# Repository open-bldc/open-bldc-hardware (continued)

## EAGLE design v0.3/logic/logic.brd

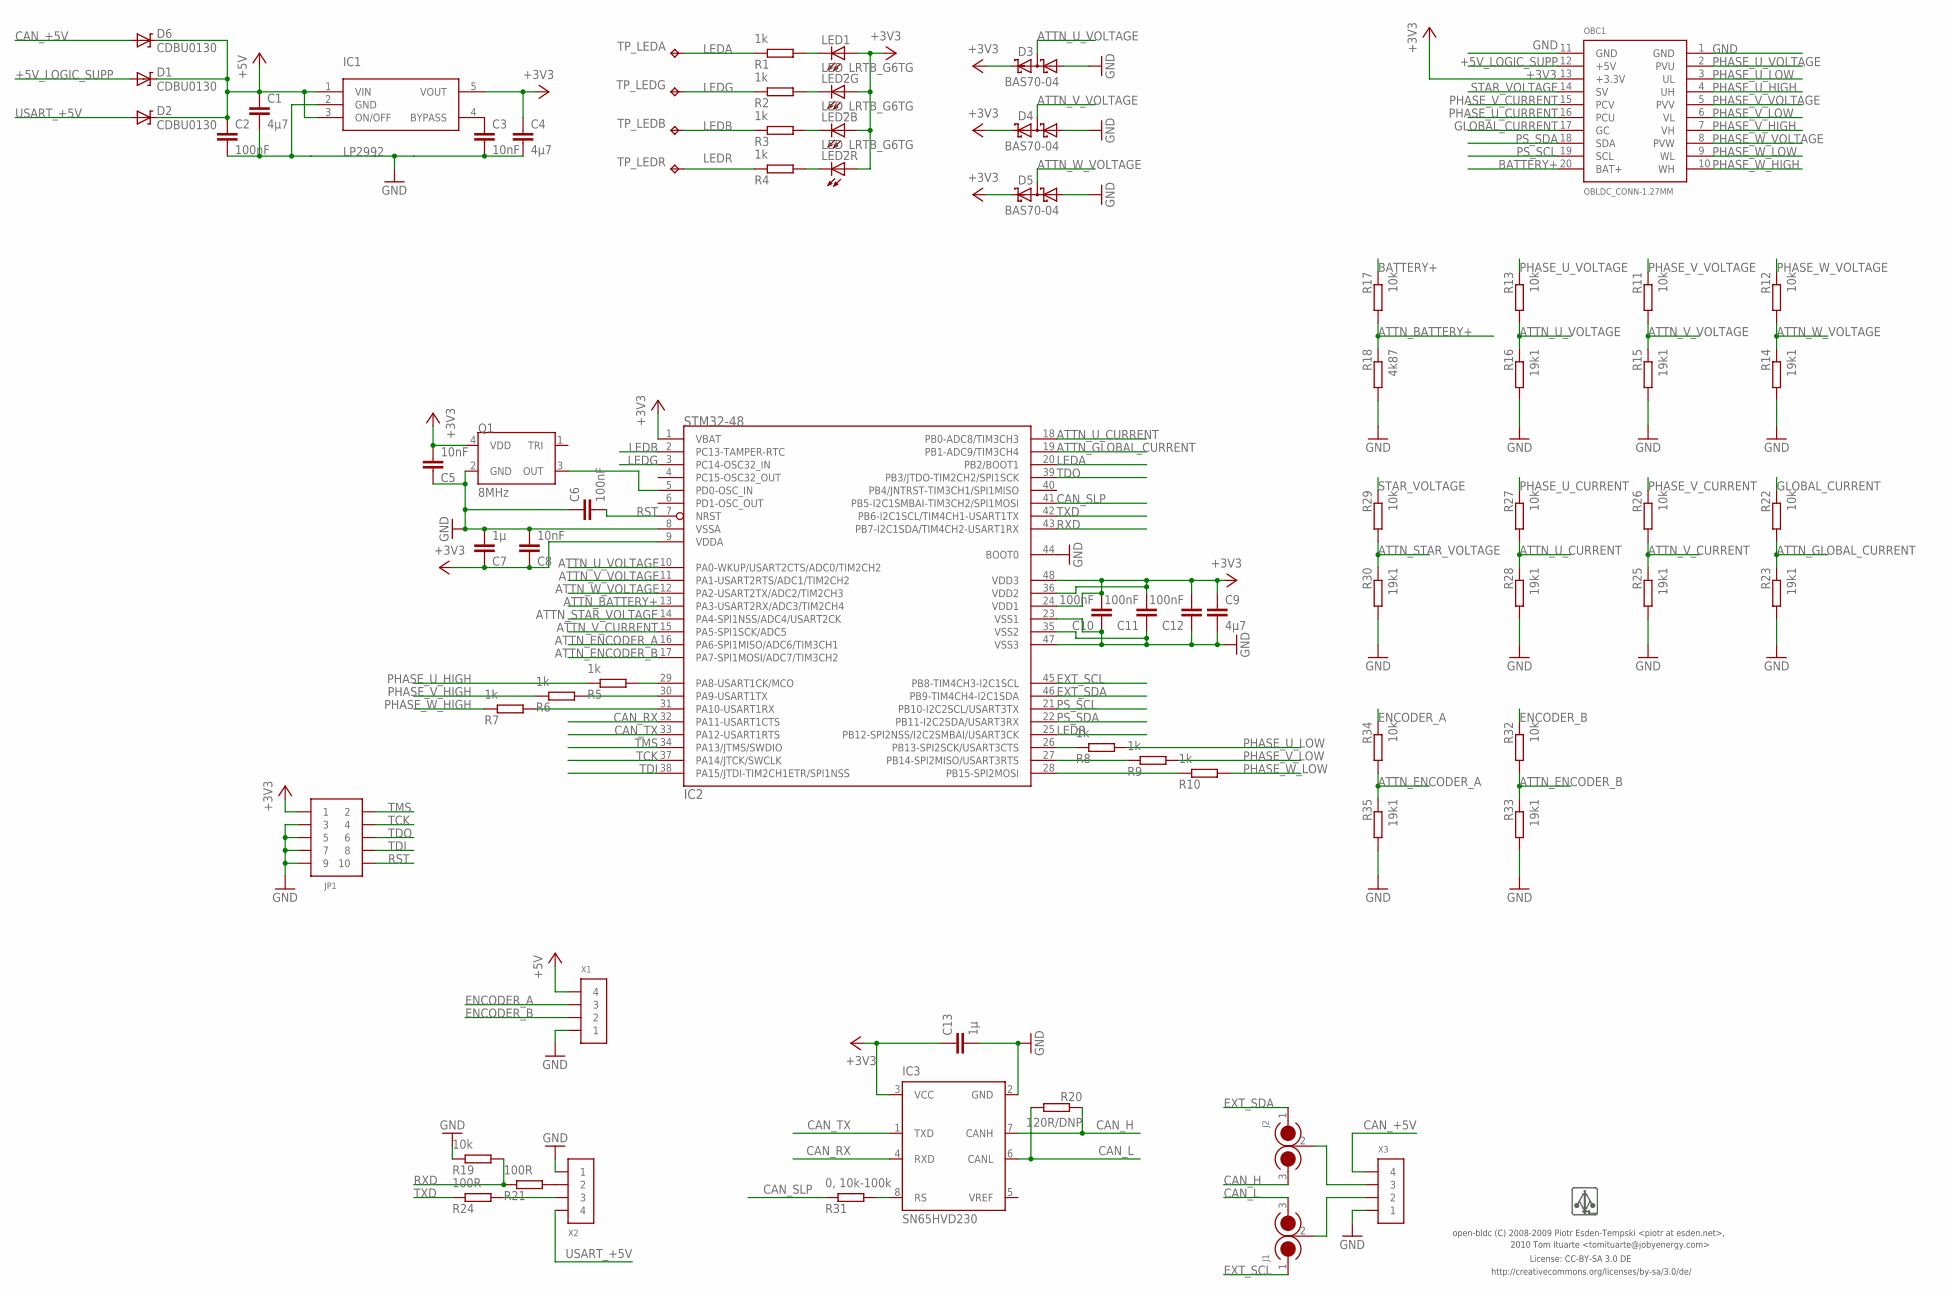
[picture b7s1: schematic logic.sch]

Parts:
C1, C4, C9: 4µ7; 0603-CAP
C2, C6, C10, C11, C12: 100nF; 0603-CAP
C3, C5, C8: 10nF; 0603-CAP
C7, C13: 1µ; 0603-CAP
D1, D2, D6: CDBU0130; 0603-LED
D3, D4, D5: BAS70-04; SOT23
IC1: LP2992; SOT23-5
IC2: STM32-48; LQFP48
IC3: SN65HVD230; SO8
J1, J2: CIRC_JMP_2
JP1: PIN_HDR_EDG_1.27MM_5-2-DH; PIN_HDR_1.27MM_SMD_DH_10
LED1: AMBER; 0603-LED
LED2: LED_LRTB_G6TG; PLCC6
OBC1: OBLDC_CONN-1.27MM; OBLDC_CONN
Q1: 8MHz; ASE_OSCILLATOR
R1, R2, R3, R4, R5, R6, R7, R8, R9, R10: 1k; 0603-RES
R11, R12, R13, R17, R19, R22, R26, R27, R29, R32, R34: 10k; 0603-RES
R14, R15, R16, R23, R25, R28, R30, R33, R35: 19k1; 0603-RES
R18: 4k87; 0603-RES
R20: 120R/DNP; 0603-RES
R21, R24: 100R; 0603-RES
R31: 0, 10k-100k; 0603-RES
TP_LEDA: TP-SMD; MINI_TESTPAD
TP_LEDB: TP-SMD; MINI_TESTPAD
TP_LEDG: TP-SMD; MINI_TESTPAD
TP_LEDR: TP-SMD; MINI_TESTPAD
U$1: LOGO
X1, X2, X3: CONN_4-1-53261; PB-53261-04

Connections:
+3V3: C4.P$1 (1), C5.P$2 (2), C7.P$1 (1), C8.P$1 (1), C9.P$1 (1), C10.P$2 (2), C11.P$2 (2), C12.P$2 (2), C13.P$1 (1), D3.2 (C2), D4.2 (C2), D5.2 (C2), IC1.5 (VOUT), IC2.1 (VBAT), IC2.9 (VDDA), IC2.24 (VDD1), IC2.36 (VDD2), IC2.48 (VDD3), IC3.3 (VCC), JP1.1, LED1.A, LED2.A1 (A), LED2.A2 (A), LED2.A3 (A), OBC1.13 (+3.3V), Q1.4 (VDD)
+5V: C1.P$1 (1), C2.P$1 (1), D1.C, D2.C, D6.C, IC1.1 (VIN), IC1.3 (ON/OFF), X1.4
+5V_LOGIC_SUPP: D1.A, OBC1.12 (+5V)
ATTN_BATTERY+: IC2.13 (PA3-USART2RX/ADC3/TIM2CH4), R17.P$2 (2), R18.P$1 (1)
ATTN_ENCODER_A: IC2.16 (PA6-SPI1MISO/ADC6/TIM3CH1), R34.P$2 (2), R35.P$1 (1)
ATTN_ENCODER_B: IC2.17 (PA7-SPI1MOSI/ADC7/TIM3CH2), R32.P$2 (2), R33.P$1 (1)
ATTN_GLOBAL_CURRENT: IC2.19 (PB1-ADC9/TIM3CH4), R22.P$2 (2), R23.P$1 (1)
ATTN_STAR_VOLTAGE: IC2.14 (PA4-SPI1NSS/ADC4/USART2CK), R29.P$2 (2), R30.P$1 (1)
ATTN_U_CURRENT: IC2.18 (PB0-ADC8/TIM3CH3), R27.P$2 (2), R28.P$1 (1)
ATTN_U_VOLTAGE: D3.3 (C1A2), IC2.10 (PA0-WKUP/USART2CTS/ADC0/TIM2CH2), R13.P$2 (2), R16.P$1 (1)
ATTN_V_CURRENT: IC2.15 (PA5-SPI1SCK/ADC5), R25.P$1 (1), R26.P$2 (2)
ATTN_V_VOLTAGE: D4.3 (C1A2), IC2.11 (PA1-USART2RTS/ADC1/TIM2CH2), R11.P$2 (2), R15.P$1 (1)
ATTN_W_VOLTAGE: D5.3 (C1A2), IC2.12 (PA2-USART2TX/ADC2/TIM2CH3), R12.P$2 (2), R14.P$1 (1)
BATTERY+: OBC1.20 (BAT+), R17.P$1 (1)
CAN_+5V: D6.A, X3.4
CAN_H: IC3.7 (CANH), J2.3, R20.P$1 (1)
CAN_L: IC3.6 (CANL), J1.3, R20.P$2 (2)
CAN_RX: IC2.32 (PA11-USART1CTS), IC3.4 (RXD)
CAN_SLP: IC2.41 (PB5-I2C1SMBAI-TIM3CH2/SPI1MOSI), R31.P$1 (1)
CAN_TX: IC2.33 (PA12-USART1RTS), IC3.1 (TXD)
ENCODER_A: R34.P$1 (1), X1.3
ENCODER_B: R32.P$1 (1), X1.2
EXT_SCL: IC2.45 (PB8-TIM4CH3-I2C1SCL), J1.1
EXT_SDA: IC2.46 (PB9-TIM4CH4-I2C1SDA), J2.1
GLOBAL_CURRENT: OBC1.17 (GC), R22.P$1 (1)
GND: C1.P$2 (2), C2.P$2 (2), C3.P$2 (2), C4.P$2 (2), C5.P$1 (1), C6.P$1 (1), C7.P$2 (2), C8.P$2 (2), C9.P$2 (2), C10.P$1 (1), C11.P$1 (1), C12.P$1 (1), C13.P$2 (2), D3.1 (A1), D4.1 (A1), D5.1 (A1), IC1.2 (GND), IC2.8 (VSSA), IC2.23 (VSS1), IC2.35 (VSS2), IC2.44 (BOOT0), IC2.47 (VSS3), IC3.2 (GND), JP1.3, JP1.5, JP1.7, JP1.9, OBC1.1 (GND), OBC1.11 (GND), Q1.2 (GND), R14.P$2 (2), R15.P$2 (2), R16.P$2 (2), R18.P$2 (2), R19.P$1 (1), R23.P$2 (2), R25.P$2 (2), R28.P$2 (2), R30.P$2 (2), R33.P$2 (2), R35.P$2 (2), X1.1, X2.1, X3.1
LEDA: IC2.20 (PB2/BOOT1), R1.P$1 (1), TP_LEDA.1
LEDB: IC2.2 (PC13-TAMPER-RTC), R3.P$1 (1), TP_LEDB.1
LEDG: IC2.3 (PC14-OSC32_IN), R2.P$1 (1), TP_LEDG.1
LEDR: IC2.25 (PB12-SPI2NSS/I2C2SMBAI/USART3CK), R4.P$1 (1), TP_LEDR.1
unnamed: J2.2, X3.3
unnamed: J1.2, X3.2
unnamed: LED1.C, R1.P$2 (2)
unnamed: LED2.C1 (C), R4.P$2 (2)
unnamed: LED2.C3 (C), R3.P$2 (2)
unnamed: R21.P$2 (2), X2.2
unnamed: IC3.8 (RS), R31.P$2 (2)
unnamed: LED2.C2 (C), R2.P$2 (2)
unnamed: R24.P$2 (2), X2.3
unnamed: C3.P$1 (1), IC1.4 (BYPASS)
unnamed: IC2.26 (PB13-SPI2SCK/USART3CTS), R8.P$1 (1)
unnamed: IC2.27 (PB14-SPI2MISO/USART3RTS), R9.P$1 (1)
unnamed: IC2.28 (PB15-SPI2MOSI), R10.P$1 (1)
unnamed: IC2.5 (PD0-OSC_IN), Q1.3 (OUT)
unnamed: IC2.29 (PA8-USART1CK/MCO), R5.P$2 (2)
unnamed: IC2.30 (PA9-USART1TX), R6.P$2 (2)
unnamed: IC2.31 (PA10-USART1RX), R7.P$2 (2)
PHASE_U_CURRENT: OBC1.16 (PCU), R27.P$1 (1)
PHASE_U_HIGH: OBC1.4 (UH), R5.P$1 (1)
PHASE_U_LOW: OBC1.3 (UL), R8.P$2 (2)
PHASE_U_VOLTAGE: OBC1.2 (PVU), R13.P$1 (1)
PHASE_V_CURRENT: OBC1.15 (PCV), R26.P$1 (1)
PHASE_V_HIGH: OBC1.7 (VH), R6.P$1 (1)
PHASE_V_LOW: OBC1.6 (VL), R9.P$2 (2)
PHASE_V_VOLTAGE: OBC1.5 (PVV), R11.P$1 (1)
PHASE_W_HIGH: OBC1.10 (WH), R7.P$1 (1)
PHASE_W_LOW: OBC1.9 (WL), R10.P$2 (2)
PHASE_W_VOLTAGE: OBC1.8 (PVW), R12.P$1 (1)
PS_SCL: IC2.21 (PB10-I2C2SCL/USART3TX), OBC1.19 (SCL)
PS_SDA: IC2.22 (PB11-I2C2SDA/USART3RX), OBC1.18 (SDA)
RST: C6.P$2 (2), IC2.7 (NRST), JP1.10
RXD: IC2.43 (PB7-I2C1SDA/TIM4CH2-USART1RX), R19.P$2 (2), R21.P$1 (1)
STAR_VOLTAGE: OBC1.14 (SV), R29.P$1 (1)
TCK: IC2.37 (PA14/JTCK/SWCLK), JP1.4
TDI: IC2.38 (PA15/JTDI-TIM2CH1ETR/SPI1NSS), JP1.8
TDO: IC2.39 (PB3/JTDO-TIM2CH2/SPI1SCK), JP1.6
TMS: IC2.34 (PA13/JTMS/SWDIO), JP1.2
TXD: IC2.42 (PB6-I2C1SCL/TIM4CH1-USART1TX), R24.P$1 (1)
USART_+5V: D2.A, X2.4

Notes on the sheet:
License: CC-BY-SA 3.0 DE
http://creativecommons.org/licenses/by-sa/3.0/de/
open-bldc (C) 2008-2009 Piotr Esden-Tempski <piotr at esden.net>,
2010 Tom Ituarte <tomituarte@jobyenergy.com>

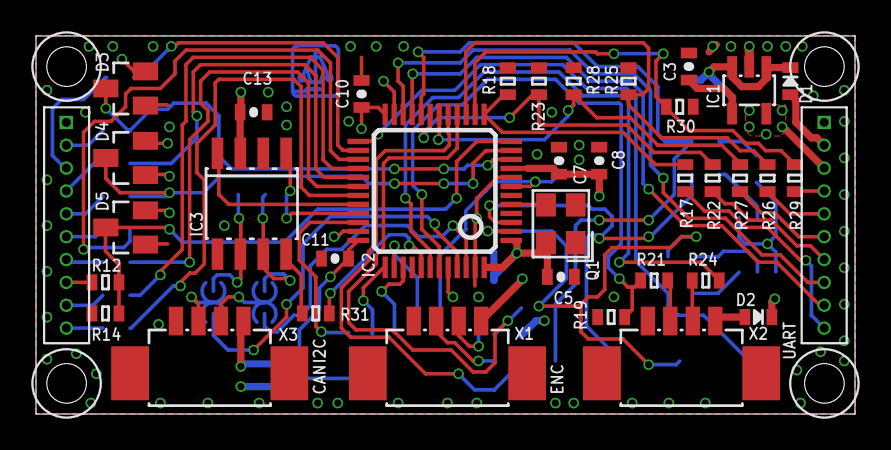
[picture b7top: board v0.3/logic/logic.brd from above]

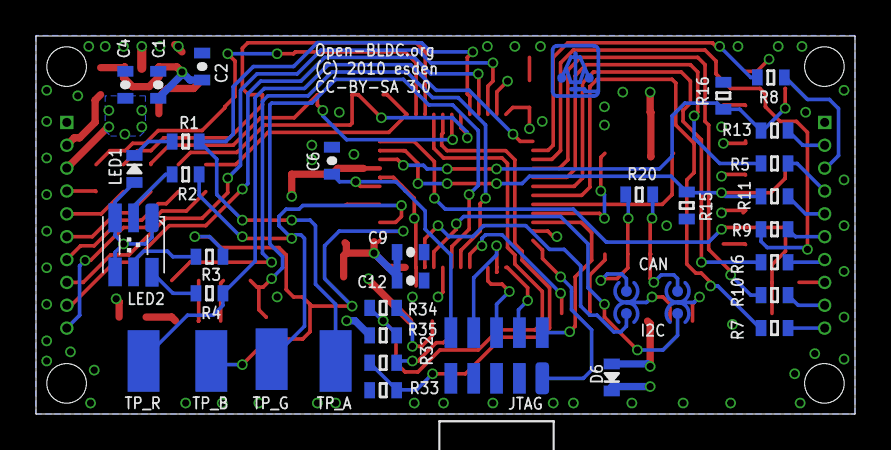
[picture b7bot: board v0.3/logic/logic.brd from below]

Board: 4 copper layers, 45.5 x 21.0 mm, 72 parts (36 on the bottom side), 69 nets.

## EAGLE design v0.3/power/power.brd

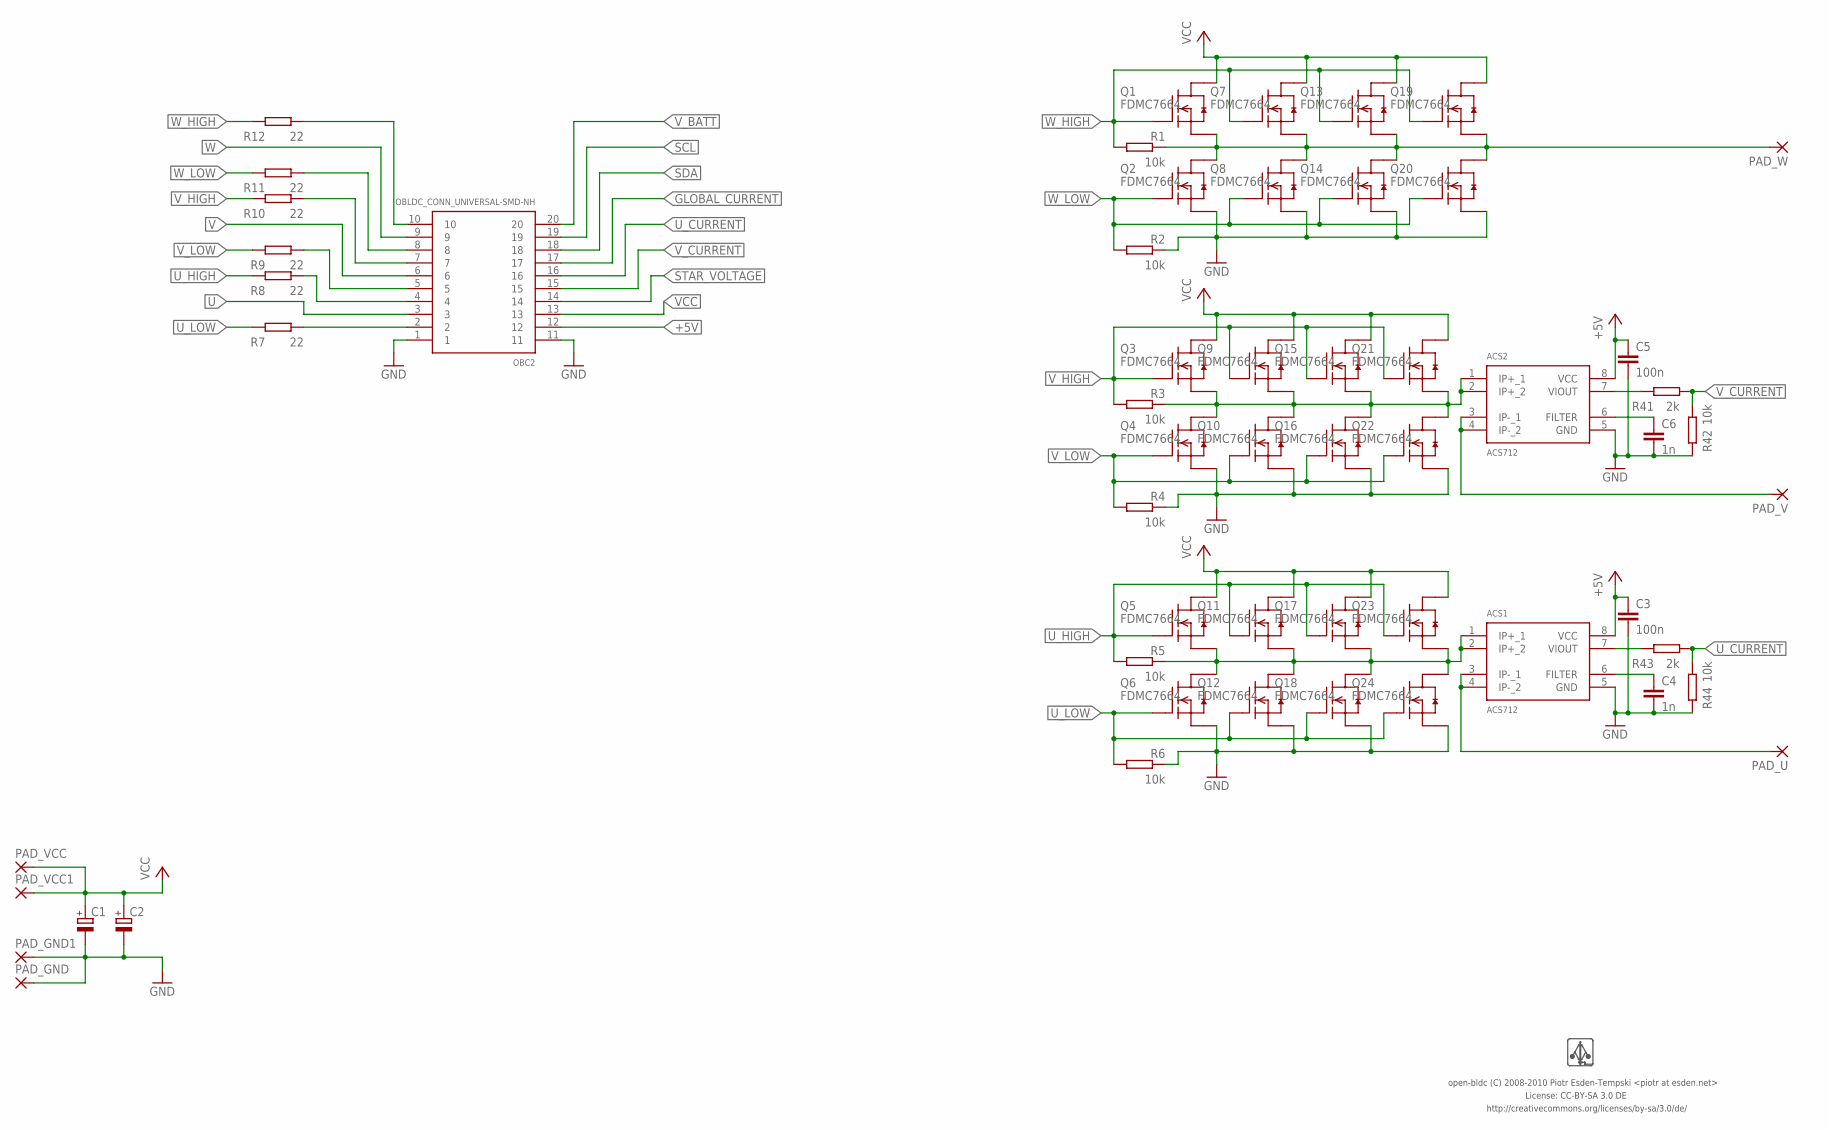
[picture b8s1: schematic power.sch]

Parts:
ACS1, ACS2: ACS712; SO8
C1, C2: CPOL-EUE5-10.5; E5-10,5
C3, C5: 100n; 0603-CAP
C4, C6: 1n; 0603-CAP
OBC2: OBLDC_CONN_UNIVERSAL-SMD-NH; OBLDC_CONN_SMD_NO_HOLES
PAD_GND, PAD_GND1: WIREPAD-2MM; WIREPAD_2MM
PAD_U: WIREPAD-2MM; WIREPAD_2MM
PAD_V: WIREPAD-2MM; WIREPAD_2MM
PAD_VCC, PAD_VCC1: WIREPAD-2MM; WIREPAD_2MM
PAD_W: WIREPAD-2MM; WIREPAD_2MM
Q1, Q2, Q3, Q4, Q5, Q6, Q7, Q8, Q9, Q10, Q11, Q12, Q13, Q14, Q15, Q16, Q17, Q18, Q19, Q20, Q21, Q22, Q23, Q24: FDMC7664; MLP33
R1, R2, R3, R4, R5, R6, R42, R44: 10k; 0603-RES
R7, R8, R9, R10, R11, R12: 22; 0603-RES
R41, R43: 2k; 0603-RES
U$2: LOGO-NORM; LOGO

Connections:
+5V: ACS1.8 (VCC), ACS2.8 (VCC), C3.P$1 (1), C5.P$1 (1), OBC2.12
GLOBAL_CURRENT: OBC2.17
GND: ACS1.5 (GND), ACS2.5 (GND), C1.-, C2.-, C3.P$2 (2), C4.P$2 (2), C5.P$2 (2), C6.P$2 (2), OBC2.1, OBC2.11, PAD_GND.1, PAD_GND1.1, Q2.123S (S), Q4.123S (S), Q6.123S (S), Q8.123S (S), Q10.123S (S), Q12.123S (S), Q14.123S (S), Q16.123S (S), Q18.123S (S), Q20.123S (S), Q22.123S (S), Q24.123S (S), R2.P$1 (1), R4.P$1 (1), R6.P$1 (1), R42.P$2 (2), R44.P$2 (2)
unnamed: ACS1.3 (IP-_1), ACS1.4 (IP-_2), PAD_U.1
unnamed: ACS2.6 (FILTER), C6.P$1 (1)
unnamed: ACS2.3 (IP-_1), ACS2.4 (IP-_2), PAD_V.1
unnamed: OBC2.2, R7.P$1 (1)
unnamed: OBC2.4, R8.P$1 (1)
unnamed: OBC2.5, R9.P$1 (1)
unnamed: OBC2.7, R10.P$1 (1)
unnamed: OBC2.8, R11.P$1 (1)
unnamed: OBC2.10, R12.P$1 (1)
unnamed: ACS1.6 (FILTER), C4.P$1 (1)
unnamed: ACS2.7 (VIOUT), R41.P$2 (2)
unnamed: ACS1.7 (VIOUT), R43.P$2 (2)
SCL: OBC2.19
SDA: OBC2.18
STAR_VOLTAGE: OBC2.14
U: ACS1.1 (IP+_1), ACS1.2 (IP+_2), OBC2.3, Q5.123S (S), Q6.5678D (D), Q11.123S (S), Q12.5678D (D), Q17.123S (S), Q18.5678D (D), Q23.123S (S), Q24.5678D (D), R5.P$1 (1)
U_CURRENT: OBC2.16, R43.P$1 (1), R44.P$1 (1)
U_HIGH: Q5.4G (G), Q11.4G (G), Q17.4G (G), Q23.4G (G), R5.P$2 (2), R8.P$2 (2)
U_LOW: Q6.4G (G), Q12.4G (G), Q18.4G (G), Q24.4G (G), R6.P$2 (2), R7.P$2 (2)
V: ACS2.1 (IP+_1), ACS2.2 (IP+_2), OBC2.6, Q3.123S (S), Q4.5678D (D), Q9.123S (S), Q10.5678D (D), Q15.123S (S), Q16.5678D (D), Q21.123S (S), Q22.5678D (D), R3.P$1 (1)
VCC: C1.+, C2.+, OBC2.13, PAD_VCC.1, PAD_VCC1.1, Q1.5678D (D), Q3.5678D (D), Q5.5678D (D), Q7.5678D (D), Q9.5678D (D), Q11.5678D (D), Q13.5678D (D), Q15.5678D (D), Q17.5678D (D), Q19.5678D (D), Q21.5678D (D), Q23.5678D (D)
V_BATT: OBC2.20
V_CURRENT: OBC2.15, R41.P$1 (1), R42.P$1 (1)
V_HIGH: Q3.4G (G), Q9.4G (G), Q15.4G (G), Q21.4G (G), R3.P$2 (2), R10.P$2 (2)
V_LOW: Q4.4G (G), Q10.4G (G), Q16.4G (G), Q22.4G (G), R4.P$2 (2), R9.P$2 (2)
W: OBC2.9, PAD_W.1, Q1.123S (S), Q2.5678D (D), Q7.123S (S), Q8.5678D (D), Q13.123S (S), Q14.5678D (D), Q19.123S (S), Q20.5678D (D), R1.P$1 (1)
W_HIGH: Q1.4G (G), Q7.4G (G), Q13.4G (G), Q19.4G (G), R1.P$2 (2), R12.P$2 (2)
W_LOW: Q2.4G (G), Q8.4G (G), Q14.4G (G), Q20.4G (G), R2.P$2 (2), R11.P$2 (2)

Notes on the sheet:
License: CC-BY-SA 3.0 DE
http://creativecommons.org/licenses/by-sa/3.0/de/
open-bldc (C) 2008-2010 Piotr Esden-Tempski <piotr at esden.net>

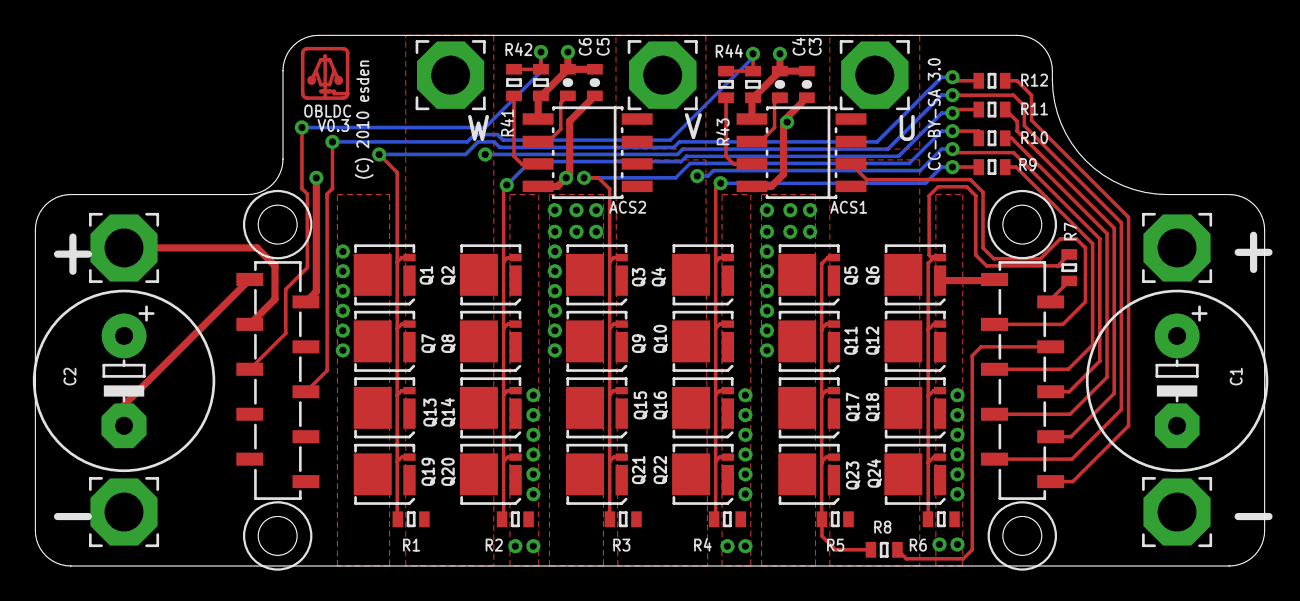
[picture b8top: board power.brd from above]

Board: 4 copper layers, 69.5 x 30.0 mm, 58 parts (0 on the bottom side), 26 nets.

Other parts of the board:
U$1: OBLDC_MECH

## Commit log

2012-07-01 Initial repository split commit. For history before that refer to the master open-bldc repository.
2012-07-01 Initial commit of the newest and shiniest low cost low power hardware!
2012-07-06 More work on strip. Preliminary routing of the power stage.
2012-07-08 Logic is on real GND now not pstage GND, to prevent current related logic signal bouncing. Added mounting holes.
2012-07-10 Some more routing on strip. Connected all the control and feedback signals from the powerstage to the MCU.
2012-07-11 All airwires routed. Now polishing can begin.
2012-07-14 Added power rail tantalum capacitor.
2012-07-15 Added silkscreen obldc logo. Put the logo and text on the pcb.
2012-07-15 Corrected size of the 4.7uF capacitor for the STM32.
2012-07-15 Added files for generating strip povray renders.
2012-08-01 Some minor silkscreen polishing.
2012-08-01 Placed part names for placement plan.
2012-08-18 Added 3v3 CAN transceiver footprint to the strip.
2012-08-18 Updated povray files with the CAN transceiver fitted.
2012-08-19 Added gerber generation files.
2012-08-19 Added jumper to (dis)connect BUSS+ and V_IN.
2012-08-20 Extended the mounting tabs to provide 4 holes. Added VScoring for removable mounting tabs.
2012-08-20 Updated povray file.
2012-08-20 Some minor adjustments and cleanups.
    - Vias in hex pattern
    - Board .5mm wider for more material between mounting holes and board
    edge.
    - Adjusted pours to use more board real estate for more copper in board.
2012-08-20 Some more layout polishing.
2012-08-20 Swapped + - wires to be the right color.
2012-08-20 Made wire display switchable.
2012-08-20 Updated pov file to the newest board version.
2012-08-20 Added panel rail files.
2012-08-20 Added some more files to gitignore.
2012-08-20 Updated/improved gerber generation files.
2012-08-20 Added tabs for panelization.
2012-09-27 Removed tabbing on the rails.
2012-09-27 More work on the BOM and part documentation.
2012-09-28 Increased size and spacing of mouse bites.
2012-09-28 Cleaned up some remaining placement plan labels.
2012-09-29 Updated strip fabdrawing notes.
2012-10-01 Fab files not needed any more as of Eagle 5. Added option for gerbmerge to disable drill size clustering!
2012-10-01 Added some more documentation to the schematic.
2012-10-08 Added more bom part number attributes.
2012-10-10 Added 2x5 panel version with top/bottom horizontal rails.
2012-10-10 Corrected position of vscore.
